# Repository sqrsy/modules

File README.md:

# What is it?

This folder contains Eurorack modules (PCBs and panels) that I designed. They are all open to use, but you must make any derivatives open too. If you use them commercially, please donate 10% of profits to a charity nearby you.

I will add detailed part lists and assembly instructions if and when I make them.

# Modules

* cv-mixer (6hp): uses an op-amp to perform attenuversion and addition on 3 inputs.
	* Parts: thonk jacks, thonk 50k pots, {560, 100k, 1M} resistors, 0.1 uF capacitors, tl074 op-amps, 10-pin power.

* logic (8hp): two sets of 2-input, 3-output logic gates: or, and, xor.
	* Parts: thonk jacks, {5k, 150k} resistors, 3mm LEDs, 4030 IC, 4071 IC, 4081 IC, 16-pin power.
	* Note: this is an imperfect module. It is missing an input comparator and an output buffer, and has untied pins on the unused logic gates.

* hocketman (8hp): an Arduino Nano Every hocket device that routes input depending on the note played.
	* Parts: thonk jacks, thonk 50k pots, thonk switches, {150k, 220k} resistors, mcp4822, 10-pin power.

* quantiser (8hp): an Arduino Nano Every dual quantiser with scale controlled by switches.
	* Parts: thonk jacks, thonk 50k pots, thonk switches, {150k, 220k} resistors, mcp4822, 10-pin power.

* rasa3x2 (10hp): a generic 2-input, 6-parameter, 4-switch, 2-output Arduino Nano Every Eurorack module shield with DAC and optional thru-zero voltage output.
	* Parts: thonk jacks, thonk 50k pots, thonk switches (optional), {330, 500, 1k, 10k, 20k, 100k} resistors, 3mm LEDs, mcp4822, 16-pin power.

* rasa6 (6hp): a generic 1-input, 2-parameter, 2-output Arduino Beetle Eurorack module shield with optional DAC.
	* Parts: thonk jacks, thonk 50k pots, {150k, 220k} resistors, mcp4822 (optional), 16-pin power.

* sn76489 (8hp): exposes the sn76489 chip as a Eurorack module.
	* Parts: thonk jacks, thonk 50k pots, thonk sub-mini switch, {150k, 220k} resistors, sn76489, 16-pin power.

* switch (3hp): a 6-jack mult that can route a 2-jack mult to one of two different sets of 2-jack mults.
	* Parts: thonk jacks, thonk sub-mini switch.

# Disclaimer

All files are provided without any guarantee. If you notice a mistake, please submit an Issue and I will fix it.

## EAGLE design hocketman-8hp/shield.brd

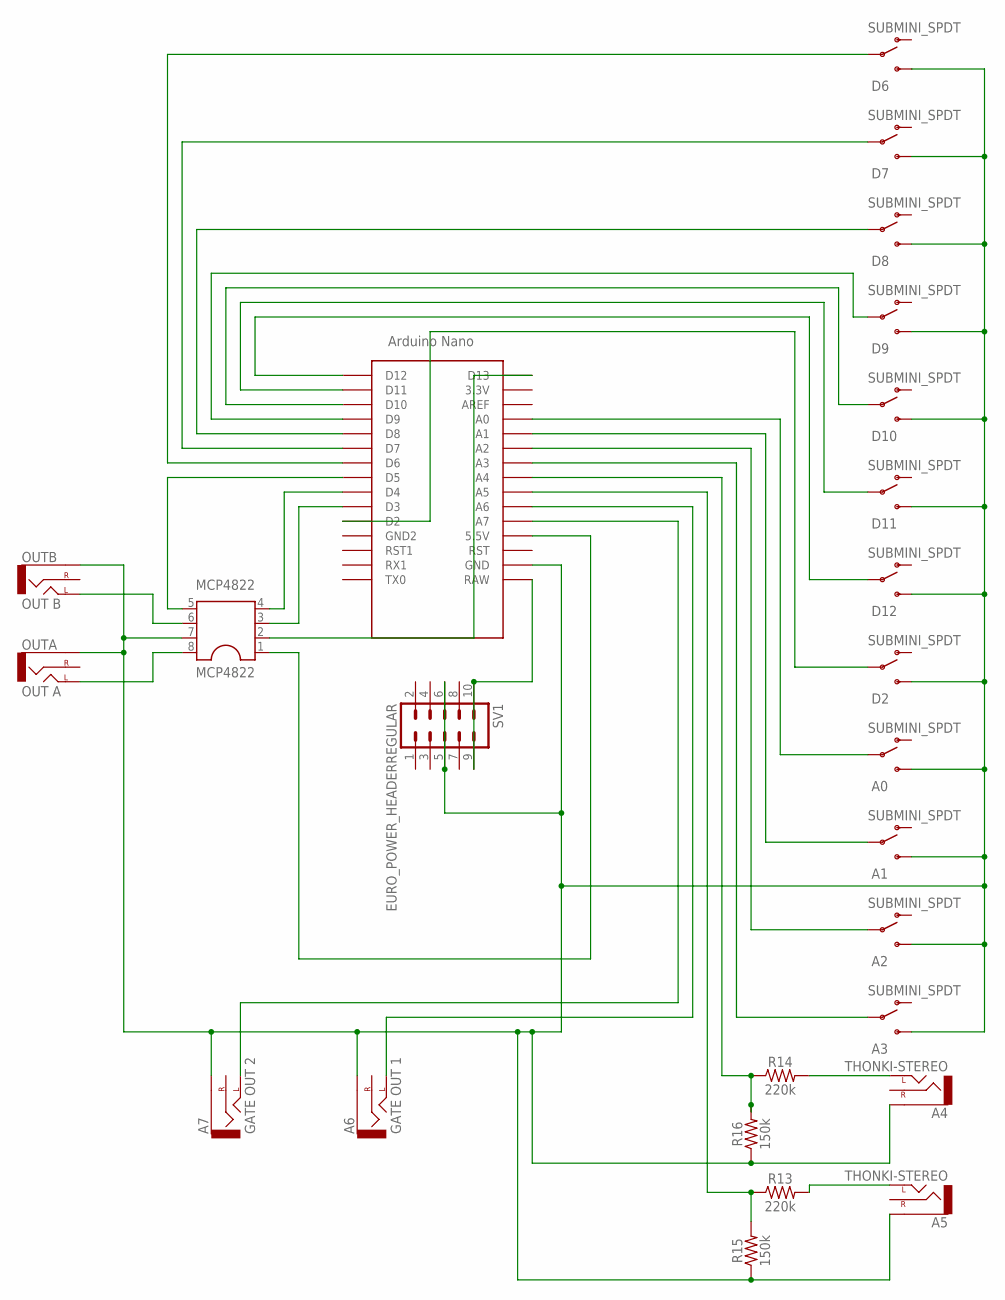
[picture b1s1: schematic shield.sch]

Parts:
A0, A1, A2, A3: SUBMINI_SPDT; SUBMINI_TOGGLE
A4, A5: THONKI-STEREO; WQP-PJ366ST_JACK
A6: GATE OUT 1; WQP-PJ366ST_JACK
A7: GATE OUT 2; WQP-PJ366ST_JACK
D2, D6, D7, D8, D9, D10, D11, D12: SUBMINI_SPDT; SUBMINI_TOGGLE
MCP4822: MCP4822; DIL08
OUTA: OUT A; WQP-PJ366ST_JACK
OUTB: OUT B; WQP-PJ366ST_JACK
R13, R14: 220k; AXIAL-0.3
R15, R16: 150k; AXIAL-0.3
SV1: EURO_POWER_HEADERREGULAR; EURO_POWER_HEADER
U$1: NANO

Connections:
unnamed: SV1.9, SV1.10, U$1.RAW
unnamed: A6.P$1_TIP (LEFT), U$1.A6
unnamed: MCP4822.1, U$1.5V (5.5V)
unnamed: D6.COM (COMMON), U$1.D6
unnamed: D7.COM (COMMON), U$1.D7
unnamed: A7.P$1_TIP (LEFT), U$1.A7
unnamed: D9.COM (COMMON), U$1.D9
unnamed: D10.COM (COMMON), U$1.D10
unnamed: D11.COM (COMMON), U$1.D11
unnamed: D12.COM (COMMON), U$1.D12
unnamed: D2.COM (COMMON), U$1.D2
unnamed: A0.COM (COMMON), U$1.A0
unnamed: A1.COM (COMMON), U$1.A1
unnamed: A2.COM (COMMON), U$1.A2
unnamed: A3.COM (COMMON), U$1.A3
unnamed: MCP4822.8, OUTA.P$1_TIP (LEFT)
unnamed: MCP4822.6, OUTB.P$1_TIP (LEFT)
unnamed: MCP4822.2, U$1.D13
unnamed: MCP4822.3, U$1.D3
unnamed: MCP4822.4, U$1.D4
unnamed: MCP4822.5, U$1.D5
unnamed: A0.3 (S), A1.3 (S), A2.3 (S), A3.3 (S), A4.P$3_SLEEVE (SLEEVE), A5.P$3_SLEEVE (SLEEVE), A6.P$3_SLEEVE (SLEEVE), A7.P$3_SLEEVE (SLEEVE), D2.3 (S), D6.3 (S), D7.3 (S), D8.3 (S), D9.3 (S), D10.3 (S), D11.3 (S), D12.3 (S), MCP4822.7, OUTA.P$3_SLEEVE (SLEEVE), OUTB.P$3_SLEEVE (SLEEVE), R15.P$1 (1), R16.P$1 (1), SV1.5, SV1.6, U$1.GND
unnamed: D8.COM (COMMON), U$1.D8
unnamed: A5.P$1_TIP (LEFT), R13.P$2 (2)
unnamed: A4.P$1_TIP (LEFT), R14.P$2 (2)
unnamed: R14.P$1 (1), R16.P$2 (2), U$1.A4
unnamed: R13.P$1 (1), R15.P$2 (2), U$1.A5

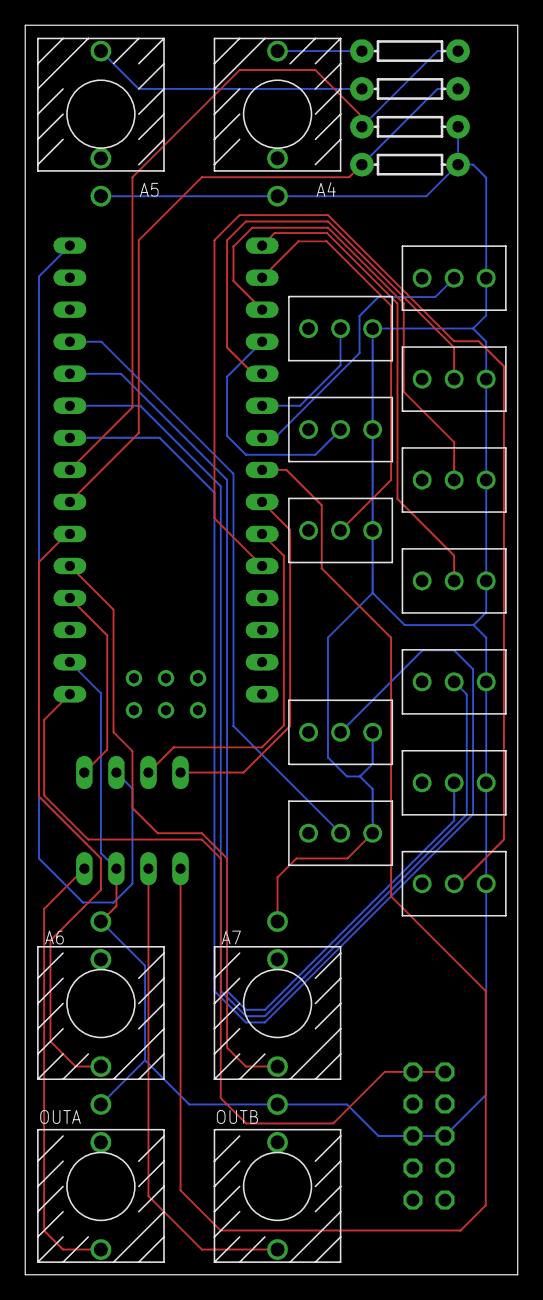
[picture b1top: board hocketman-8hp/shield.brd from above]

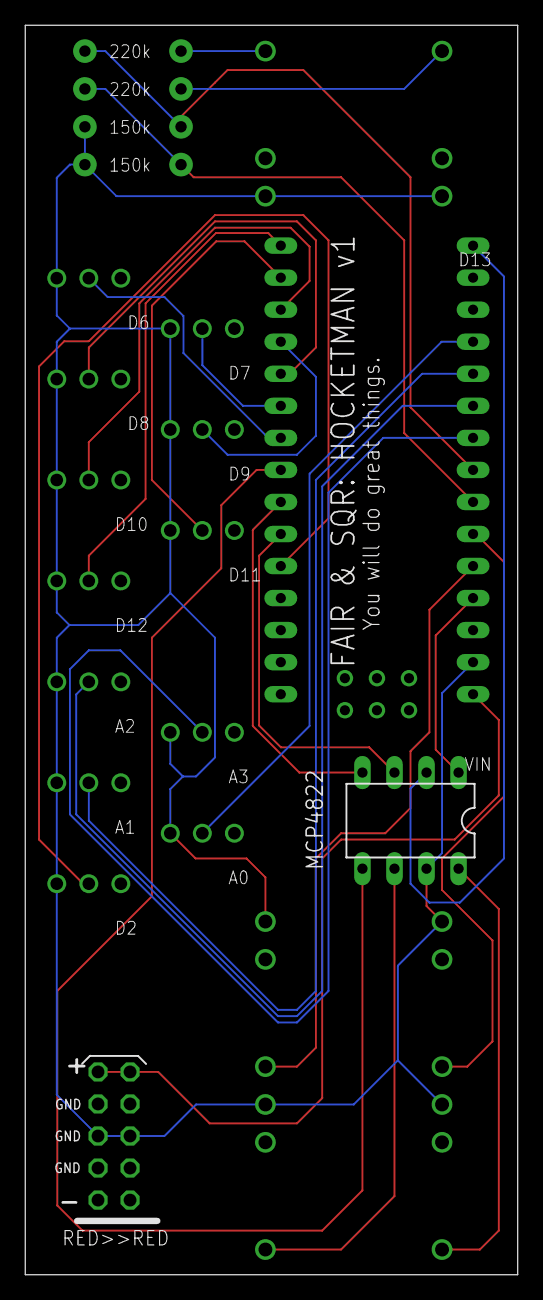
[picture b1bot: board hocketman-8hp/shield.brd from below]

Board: 2 copper layers, 39.0 x 99.0 mm, 25 parts (2 on the bottom side), 27 nets.

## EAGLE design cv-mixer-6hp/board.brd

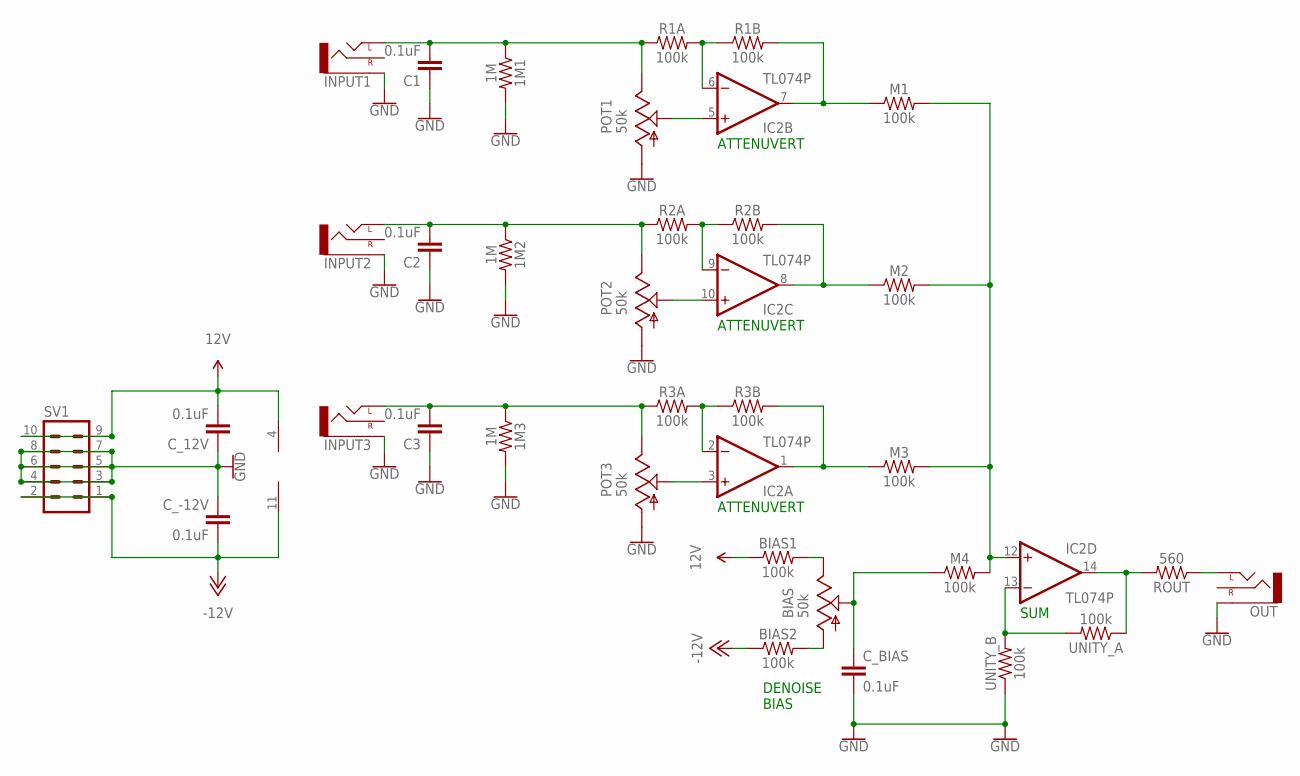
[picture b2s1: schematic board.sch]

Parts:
1M1, 1M2, 1M3: 1M; AXIAL-0.3
BIAS: 50k; 9MM_SNAP-IN_POT
BIAS1, BIAS2: 100k; AXIAL-0.3
C1, C2, C3: 0.1uF; CAP-PTH-SMALL-KIT
C_12V: 0.1uF; CAP-PTH-SMALL-KIT
C_-12V: 0.1uF; CAP-PTH-SMALL-KIT
C_BIAS: 0.1uF; CAP-PTH-SMALL-KIT
IC2: TL074P; DIL14
INPUT1, INPUT2, INPUT3: THONKI-STEREO; WQP-PJ366ST_JACK
M1, M2, M3, M4: 100k; AXIAL-0.3
OUT: THONKI-STEREO; WQP-PJ366ST_JACK
POT1, POT2, POT3: 50k; 9MM_SNAP-IN_POT
R1A, R1B, R2A, R2B, R3A, R3B: 100k; AXIAL-0.3
ROUT: 560; AXIAL-0.3
SV1: EURO_POWER_HEADERFAT_PADS; EURO_PWR_HEADER_FAT
UNITY_A: 100k; AXIAL-0.3
UNITY_B: 100k; AXIAL-0.3

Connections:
12V: BIAS1.P$1 (1), C_12V.2, IC2.4 (V+), SV1.9, SV1.10
-12V: BIAS2.P$1 (1), C_-12V.2, IC2.11 (V-), SV1.1, SV1.2
GND: 1M1.P$2 (2), 1M2.P$2 (2), 1M3.P$2 (2), C1.1, C2.1, C3.1, C_12V.1, C_-12V.1, C_BIAS.2, INPUT1.P$3_SLEEVE (SLEEVE), INPUT2.P$3_SLEEVE (SLEEVE), INPUT3.P$3_SLEEVE (SLEEVE), OUT.P$3_SLEEVE (SLEEVE), POT1.1 (A), POT2.1 (A), POT3.1 (A), SV1.3, SV1.4, SV1.5, SV1.6, SV1.7, SV1.8, UNITY_B.P$1 (1)
unnamed: OUT.P$1_TIP (LEFT), ROUT.P$1 (1)
unnamed: IC2.14 (OUT), ROUT.P$2 (2), UNITY_A.P$1 (1)
unnamed: BIAS.3 (E), BIAS1.P$2 (2)
unnamed: BIAS.1 (A), BIAS2.P$2 (2)
unnamed: BIAS.2 (S), C_BIAS.1, M4.P$1 (1)
unnamed: IC2.12 (+IN), M1.P$2 (2), M2.P$2 (2), M3.P$2 (2), M4.P$2 (2)
unnamed: IC2.13 (-IN), UNITY_A.P$2 (2), UNITY_B.P$2 (2)
unnamed: IC2.7 (OUT), M1.P$1 (1), R1B.P$2 (2)
unnamed: IC2.6 (-IN), R1A.P$2 (2), R1B.P$1 (1)
unnamed: 1M1.P$1 (1), C1.2, INPUT1.P$1_TIP (LEFT), POT1.3 (E), R1A.P$1 (1)
unnamed: IC2.5 (+IN), POT1.2 (S)
unnamed: IC2.8 (OUT), M2.P$1 (1), R2B.P$2 (2)
unnamed: IC2.9 (-IN), R2A.P$2 (2), R2B.P$1 (1)
unnamed: 1M2.P$1 (1), C2.2, INPUT2.P$1_TIP (LEFT), POT2.3 (E), R2A.P$1 (1)
unnamed: IC2.10 (+IN), POT2.2 (S)
unnamed: IC2.1 (OUT), M3.P$1 (1), R3B.P$2 (2)
unnamed: IC2.2 (-IN), R3A.P$2 (2), R3B.P$1 (1)
unnamed: 1M3.P$1 (1), C3.2, INPUT3.P$1_TIP (LEFT), POT3.3 (E), R3A.P$1 (1)
unnamed: IC2.3 (+IN), POT3.2 (S)

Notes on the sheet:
SUM
DENOISE BIAS
ATTENUVERT

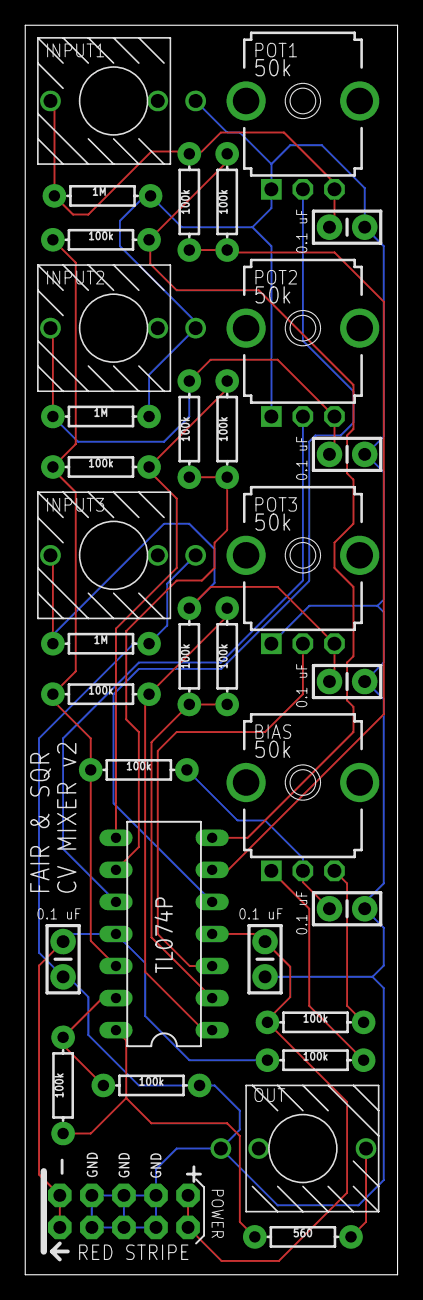
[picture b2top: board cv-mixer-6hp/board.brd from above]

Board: 2 copper layers, 29.5 x 99.0 mm, 34 parts (0 on the bottom side), 22 nets.

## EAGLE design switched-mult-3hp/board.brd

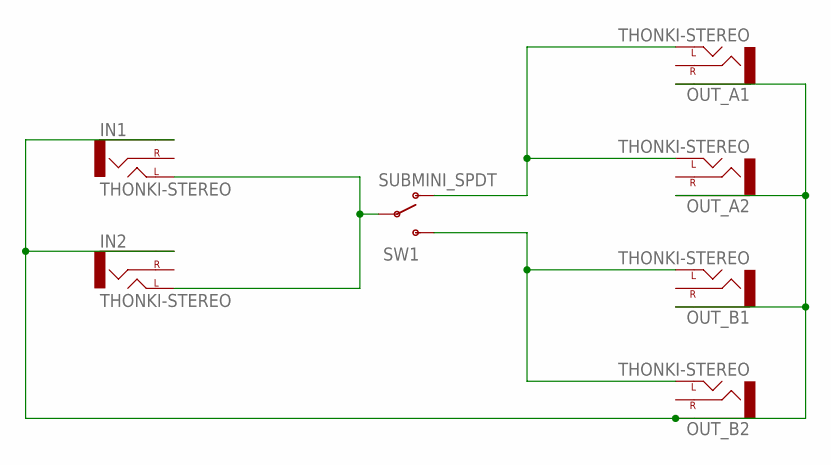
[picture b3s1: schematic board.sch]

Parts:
IN1, IN2: THONKI-STEREO; WQP-PJ366ST_JACK
OUT_A1, OUT_A2: THONKI-STEREO; WQP-PJ366ST_JACK
OUT_B1, OUT_B2: THONKI-STEREO; WQP-PJ366ST_JACK
SW1: SUBMINI_SPDT; SUBMINI_TOGGLE

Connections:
unnamed: IN1.P$1_TIP (LEFT), IN2.P$1_TIP (LEFT), SW1.COM (COMMON)
unnamed: OUT_A1.P$1_TIP (LEFT), OUT_A2.P$1_TIP (LEFT), SW1.1 (O)
unnamed: OUT_B1.P$1_TIP (LEFT), OUT_B2.P$1_TIP (LEFT), SW1.3 (S)
unnamed: IN1.P$3_SLEEVE (SLEEVE), IN2.P$3_SLEEVE (SLEEVE), OUT_A1.P$3_SLEEVE (SLEEVE), OUT_A2.P$3_SLEEVE (SLEEVE), OUT_B1.P$3_SLEEVE (SLEEVE), OUT_B2.P$3_SLEEVE (SLEEVE)

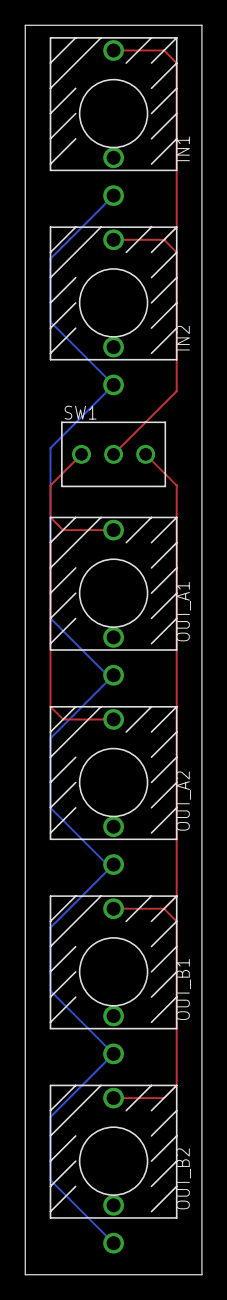
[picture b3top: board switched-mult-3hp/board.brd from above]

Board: 2 copper layers, 14.0 x 99.0 mm, 7 parts (0 on the bottom side), 4 nets.

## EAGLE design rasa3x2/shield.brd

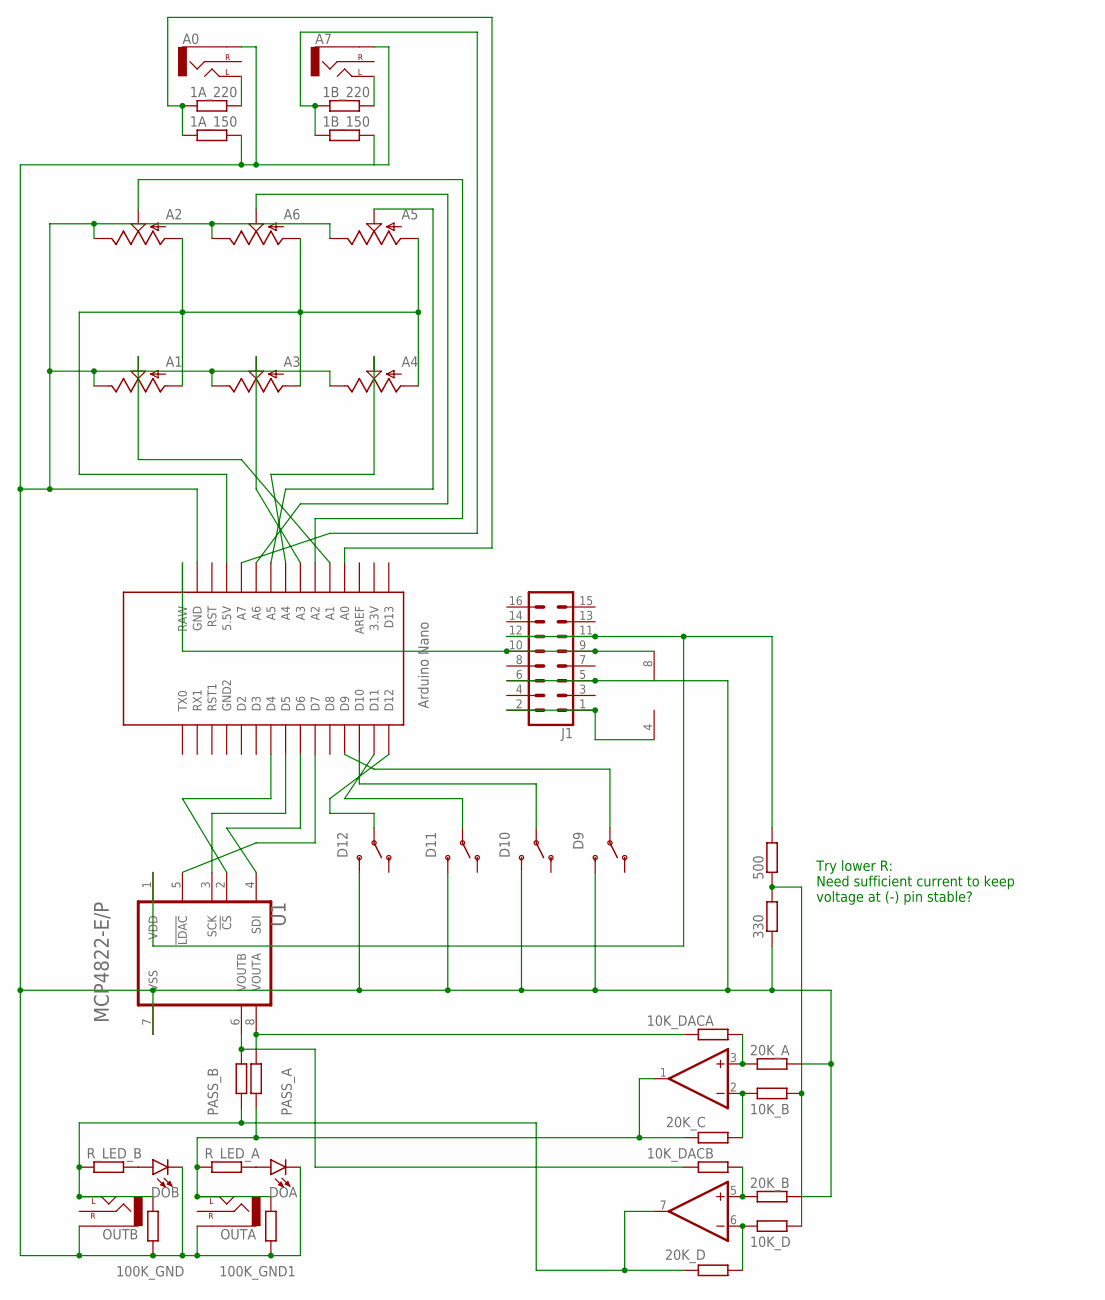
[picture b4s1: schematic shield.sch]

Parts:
1A_150, 1A_220, 1B_150, 1B_220, 10K_B, 10K_D, 10K_DACA, 10K_DACB, 20K_A, 20K_B, 20K_C, 20K_D, 100K_GND, 100K_GND1, 330, 500: RESISTOR7MM; 7MM_RESISTOR
A0, A7: THONKI-STEREO; WQP-PJ366ST_JACK
A1, A2, A3, A4, A5, A6: 9MM_SNAP-IN_POT_; 9MM_SNAP-IN_POT
D9, D10, D11, D12: SUBMINI_SPDT; SUBMINI_TOGGLE
DOA: LED3MM; LED_3MM
DOB: LED3MM; LED_3MM
IC1: TL072P; DIL08
J1: CONN_08X2; 2X8
OUTA: THONKI-STEREO; WQP-PJ366ST_JACK
OUTB: THONKI-STEREO; WQP-PJ366ST_JACK
PASS_A: RESISTOR7MM; 7MM_RESISTOR
PASS_B: RESISTOR7MM; 7MM_RESISTOR
R_LED_A: RESISTOR7MM; 7MM_RESISTOR
R_LED_B: RESISTOR7MM; 7MM_RESISTOR
U1: MICROCHIP_MCP4822-E-PMICROCHIP_MCP4822-E-P_0_0; MICROCHIP_MCP4822-E-P_0
U$1: NANO

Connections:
unnamed: D12.COM (COMMON), U$1.D12
unnamed: D11.COM (COMMON), U$1.D11
unnamed: A1.2 (S), U$1.A1
unnamed: 1A_150.2, 1B_150.2, 20K_A.2, 20K_B.2, 100K_GND.2, 100K_GND1.2, 330.1, A0.P$3_SLEEVE (SLEEVE), A1.3 (E), A2.3 (E), A3.3 (E), A4.3 (E), A5.3 (E), A6.3 (E), A7.P$3_SLEEVE (SLEEVE), D9.3 (S), D10.3 (S), D11.3 (S), D12.3 (S), DOA.K (C), DOB.K (C), J1.5, J1.6, OUTA.P$3_SLEEVE (SLEEVE), OUTB.P$3_SLEEVE (SLEEVE), U1.7 (VSS), U$1.GND
unnamed: D10.COM (COMMON), U$1.D10
unnamed: 1A_150.1, 1A_220.1, U$1.A0
unnamed: 1A_220.2, A0.P$1_TIP (LEFT)
unnamed: A1.1 (A), A2.1 (A), A3.1 (A), A4.1 (A), A5.1 (A), A6.1 (A), U$1.5V (5.5V)
unnamed: A2.2 (S), U$1.A2
unnamed: IC1.4 (V-), J1.1, J1.2
unnamed: A3.2 (S), U$1.A3
unnamed: A6.2 (S), U$1.A6
unnamed: 10K_DACA.1, PASS_A.2, U1.8 (VOUTA)
unnamed: 10K_DACB.1, PASS_B.2, U1.6 (VOUTB)
unnamed: A4.2 (S), U$1.A4
unnamed: 1B_150.1, 1B_220.1, U$1.A7
unnamed: A5.2 (S), U$1.A5
unnamed: 20K_C.2, 100K_GND1.1, IC1.1 (OUT), OUTA.P$1_TIP (LEFT), PASS_A.1, R_LED_A.1
unnamed: D9.COM (COMMON), U$1.D9
unnamed: 10K_D.1, 20K_D.1, IC1.6 (-IN)
unnamed: 10K_DACA.2, 20K_A.1, IC1.3 (+IN)
unnamed: 10K_B.1, 20K_C.1, IC1.2 (-IN)
unnamed: 10K_DACB.2, 20K_B.1, IC1.5 (+IN)
unnamed: 1B_220.2, A7.P$1_TIP (LEFT)
unnamed: 10K_B.2, 10K_D.2, 330.2, 500.1
unnamed: 20K_D.2, 100K_GND.1, IC1.7 (OUT), OUTB.P$1_TIP (LEFT), PASS_B.1, R_LED_B.1
unnamed: U1.2 (!CS!), U$1.D4
unnamed: U1.3 (SCK), U$1.D5
unnamed: U1.4 (SDI), U$1.D6
unnamed: U1.5 (!LDAC!), U$1.D7
unnamed: DOB.A, R_LED_B.2
unnamed: DOA.A, R_LED_A.2
unnamed: 500.2, J1.11, J1.12, U1.1 (VDD)
unnamed: IC1.8 (V+), J1.9, J1.10, U$1.RAW

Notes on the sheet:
Try lower R: Need sufficient current to keep voltage at (-) pin stable?

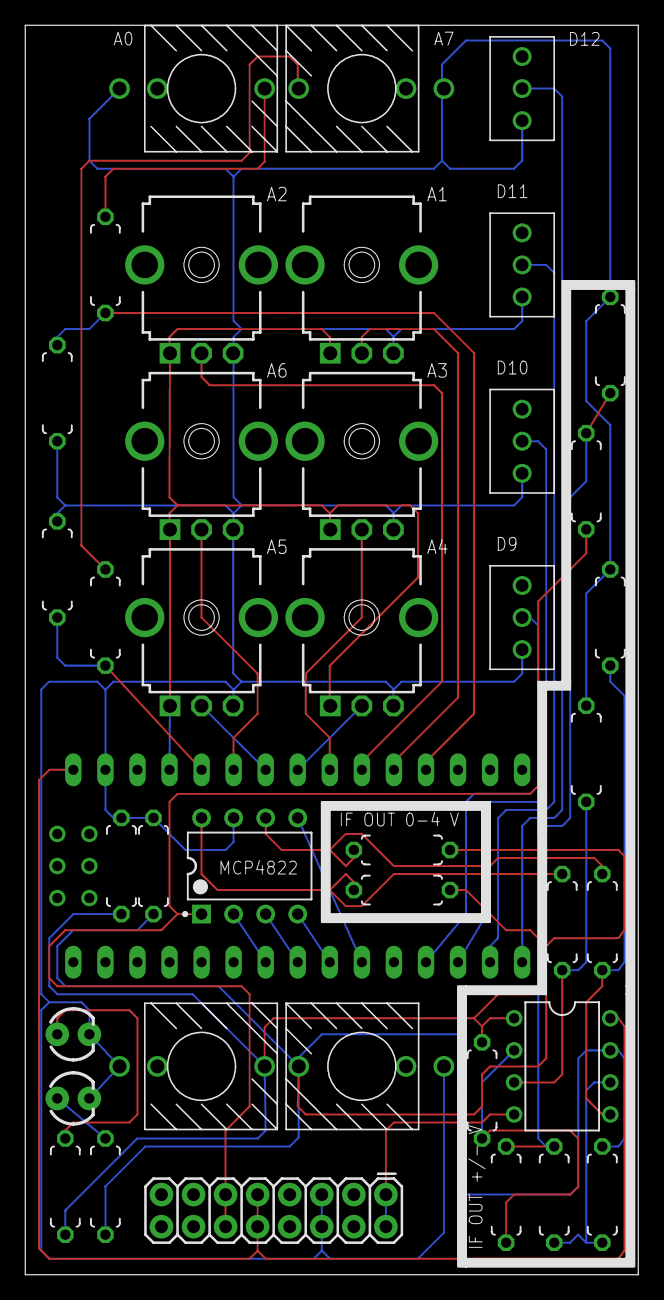
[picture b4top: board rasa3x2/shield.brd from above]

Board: 2 copper layers, 48.6 x 99.0 mm, 40 parts (0 on the bottom side), 34 nets.

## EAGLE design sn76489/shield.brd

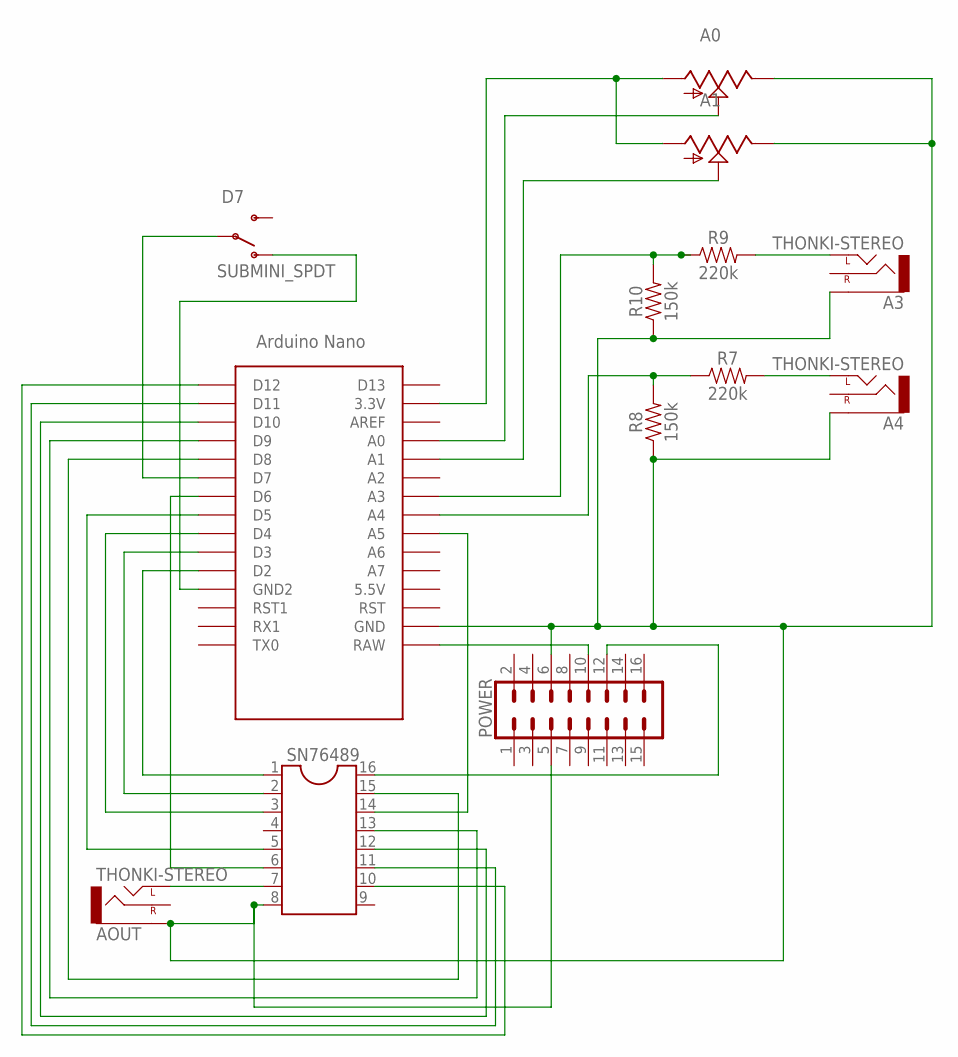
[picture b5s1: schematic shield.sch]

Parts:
A0, A1: 9MM_SNAP-IN_POT_; 9MM_SNAP-IN_POT
A3, A4: THONKI-STEREO; WQP-PJ366ST_JACK
AOUT: THONKI-STEREO; WQP-PJ366ST_JACK
D7: SUBMINI_SPDT; SUBMINI_TOGGLE
POWER: CONN_08X2; 2X8
R7, R9: 220k; AXIAL-0.3-KIT
R8, R10: 150k; AXIAL-0.3-KIT
SN76489: DIL16
U$1: NANO

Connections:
unnamed: SN76489.14, U$1.A5
unnamed: POWER.12, SN76489.16
unnamed: A0.1 (A), A1.1 (A), U$1.3.3V
unnamed: SN76489.5, U$1.D5
unnamed: SN76489.6, U$1.D6
unnamed: SN76489.3, U$1.D4
unnamed: SN76489.1, U$1.D2
unnamed: SN76489.2, U$1.D3
unnamed: POWER.10, U$1.RAW
unnamed: A3.P$1_TIP (LEFT), R9.P$2 (2)
unnamed: AOUT.P$1_TIP (LEFT), SN76489.7
unnamed: SN76489.10, U$1.D12
unnamed: D7.1 (O), U$1.GND1 (GND2)
unnamed: A0.2 (S), U$1.A0
unnamed: A1.2 (S), U$1.A1
unnamed: R9.P$1 (1), R10.P$2 (2), U$1.A3
unnamed: A4.P$1_TIP (LEFT), R7.P$2 (2)
unnamed: R7.P$1 (1), R8.P$2 (2), U$1.A4
unnamed: D7.COM (COMMON), U$1.D7
unnamed: A0.3 (E), A1.3 (E), A3.P$3_SLEEVE (SLEEVE), A4.P$3_SLEEVE (SLEEVE), AOUT.P$3_SLEEVE (SLEEVE), POWER.5, POWER.6, R8.P$1 (1), R10.P$1 (1), SN76489.8, U$1.GND
unnamed: SN76489.11, U$1.D11
unnamed: SN76489.13, U$1.D9
unnamed: SN76489.15, U$1.D8
unnamed: SN76489.12, U$1.D10

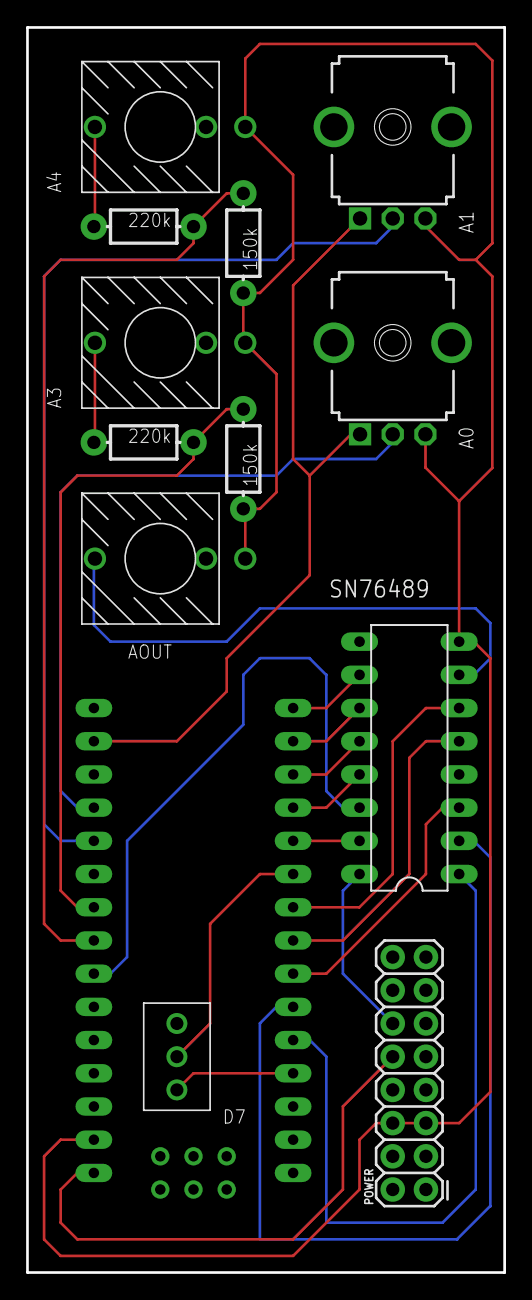
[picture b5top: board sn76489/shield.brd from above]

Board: 2 copper layers, 36.5 x 95.2 mm, 13 parts (0 on the bottom side), 24 nets.

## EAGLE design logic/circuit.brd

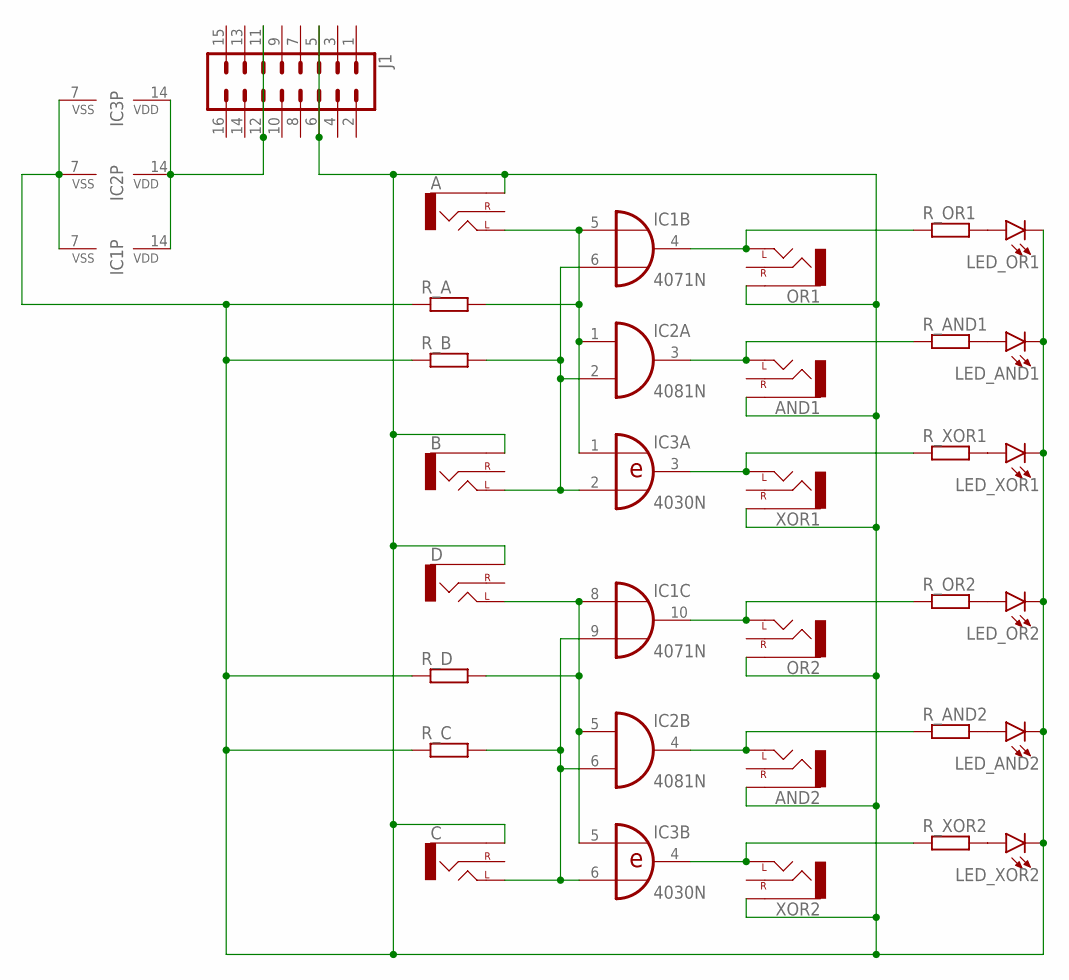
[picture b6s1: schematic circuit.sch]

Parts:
A: THONKI-STEREO; WQP-PJ366ST_JACK
AND1, AND2: THONKI-STEREO; WQP-PJ366ST_JACK
B: THONKI-STEREO; WQP-PJ366ST_JACK
C: THONKI-STEREO; WQP-PJ366ST_JACK
D: THONKI-STEREO; WQP-PJ366ST_JACK
IC1: 4071N; DIL14
IC2: 4081N; DIL14
IC3: 4030N; DIL14
J1: CONN_08X2; 2X8
LED_AND1, LED_AND2: LED3MM; LED_3MM
LED_OR1, LED_OR2: LED3MM; LED_3MM
LED_XOR1, LED_XOR2: LED3MM; LED_3MM
OR1, OR2: THONKI-STEREO; WQP-PJ366ST_JACK
R_A: RESISTOR7MM; 7MM_RESISTOR
R_AND1, R_AND2: RESISTOR7MM; 7MM_RESISTOR
R_B: RESISTOR7MM; 7MM_RESISTOR
R_C: RESISTOR7MM; 7MM_RESISTOR
R_D: RESISTOR7MM; 7MM_RESISTOR
R_OR1, R_OR2: RESISTOR7MM; 7MM_RESISTOR
R_XOR1, R_XOR2: RESISTOR7MM; 7MM_RESISTOR
XOR1, XOR2: THONKI-STEREO; WQP-PJ366ST_JACK

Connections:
LED_OR1: A.P$3_SLEEVE (SLEEVE), AND1.P$3_SLEEVE (SLEEVE), AND2.P$3_SLEEVE (SLEEVE), B.P$3_SLEEVE (SLEEVE), C.P$3_SLEEVE (SLEEVE), D.P$3_SLEEVE (SLEEVE), IC1.7 (VSS), IC2.7 (VSS), IC3.7 (VSS), J1.5, J1.6, LED_AND1.K (C), LED_AND2.K (C), LED_OR1.K (C), LED_OR2.K (C), LED_XOR1.K (C), LED_XOR2.K (C), OR1.P$3_SLEEVE (SLEEVE), OR2.P$3_SLEEVE (SLEEVE), R_A.1, R_B.1, R_C.1, R_D.1, XOR1.P$3_SLEEVE (SLEEVE), XOR2.P$3_SLEEVE (SLEEVE)
unnamed: LED_OR1.A, R_OR1.2
unnamed: LED_AND1.A, R_AND1.2
unnamed: IC1.14 (VDD), IC2.14 (VDD), IC3.14 (VDD), J1.11, J1.12
unnamed: LED_XOR1.A, R_XOR1.2
unnamed: LED_OR2.A, R_OR2.2
unnamed: LED_AND2.A, R_AND2.2
unnamed: LED_XOR2.A, R_XOR2.2
unnamed: IC3.4 (O), R_XOR2.1, XOR2.P$1_TIP (LEFT)
unnamed: AND2.P$1_TIP (LEFT), IC2.4 (O), R_AND2.1
unnamed: IC1.10 (O), OR2.P$1_TIP (LEFT), R_OR2.1
unnamed: IC3.3 (O), R_XOR1.1, XOR1.P$1_TIP (LEFT)
unnamed: AND1.P$1_TIP (LEFT), IC2.3 (O), R_AND1.1
unnamed: IC1.4 (O), OR1.P$1_TIP (LEFT), R_OR1.1
unnamed: A.P$1_TIP (LEFT), IC1.5 (I0), IC2.1 (I0), IC3.1 (I0), R_A.2
unnamed: B.P$1_TIP (LEFT), IC1.6 (I1), IC2.2 (I1), IC3.2 (I1), R_B.2
unnamed: D.P$1_TIP (LEFT), IC1.8 (I0), IC2.5 (I0), IC3.5 (I0), R_D.2
unnamed: C.P$1_TIP (LEFT), IC1.9 (I1), IC2.6 (I1), IC3.6 (I1), R_C.2

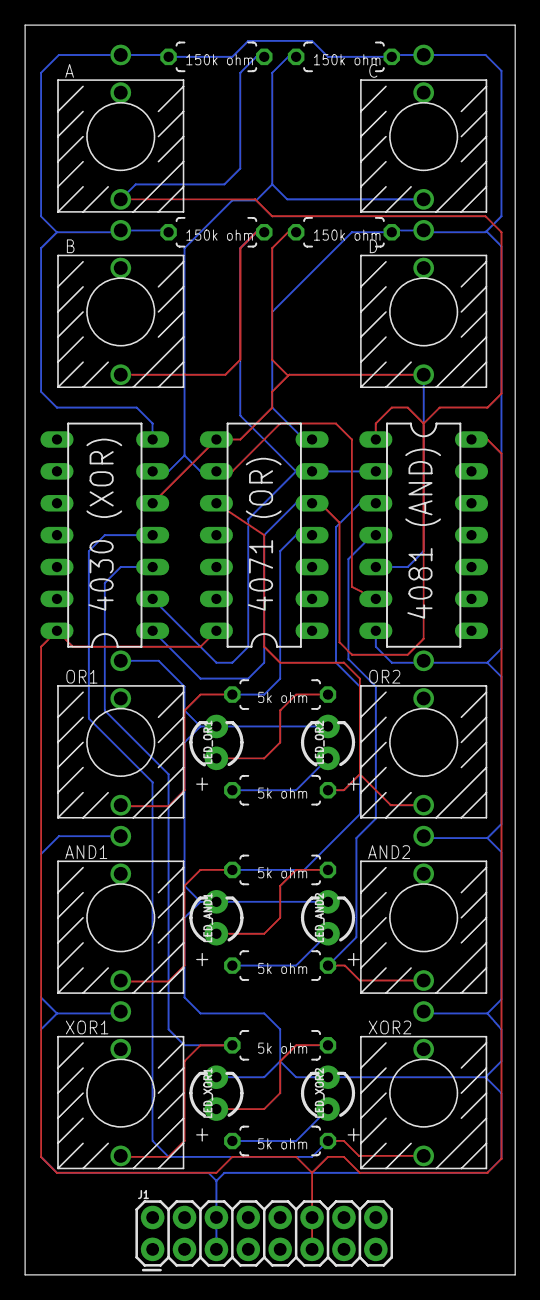
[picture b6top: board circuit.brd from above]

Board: 2 copper layers, 39.0 x 99.6 mm, 30 parts (0 on the bottom side), 18 nets.

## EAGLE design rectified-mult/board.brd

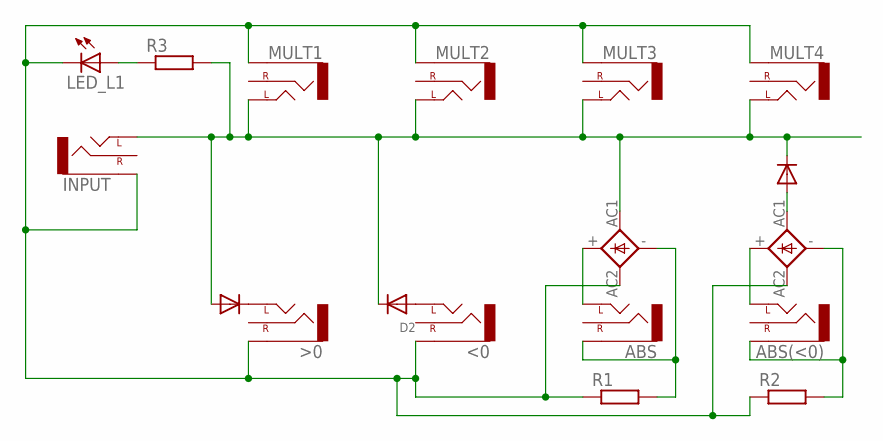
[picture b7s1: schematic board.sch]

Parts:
<0: THONKI-STEREO; WQP-PJ366ST_JACK
>0: THONKI-STEREO; WQP-PJ366ST_JACK
ABS: THONKI-STEREO; WQP-PJ366ST_JACK
ABS(<0): THONKI-STEREO; WQP-PJ366ST_JACK
B1, B2: 2KBB-R
D1, D2, D3: DIODEDO-1N4148; DO-1N4148
INPUT: THONKI-STEREO; WQP-PJ366ST_JACK
LED_L1: LED3MM
MULT1, MULT2, MULT3, MULT4: THONKI-STEREO; WQP-PJ366ST_JACK
R1, R2, R3: RESISTOR7MM; 7MM_RESISTOR

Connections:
unnamed: ABS(<0).P$1_TIP (LEFT), B2.+
unnamed: >0.P$1_TIP (LEFT), D1.C
unnamed: B2.AC1, D3.A
unnamed: LED_L1.A, R3.1
unnamed: <0.P$1_TIP (LEFT), D2.A
unnamed: B1.AC1, D1.A, D2.C, D3.C, INPUT.P$1_TIP (LEFT), MULT1.P$1_TIP (LEFT), MULT2.P$1_TIP (LEFT), MULT3.P$1_TIP (LEFT), MULT4.P$1_TIP (LEFT), R3.2
unnamed: <0.P$3_SLEEVE (SLEEVE), >0.P$3_SLEEVE (SLEEVE), B1.AC2, B2.AC2, INPUT.P$3_SLEEVE (SLEEVE), LED_L1.K (C), MULT1.P$3_SLEEVE (SLEEVE), MULT2.P$3_SLEEVE (SLEEVE), MULT3.P$3_SLEEVE (SLEEVE), MULT4.P$3_SLEEVE (SLEEVE), R1.1, R2.1
unnamed: ABS.P$3_SLEEVE (SLEEVE), B1.-, R1.2
unnamed: ABS.P$1_TIP (LEFT), B1.+
unnamed: ABS(<0).P$3_SLEEVE (SLEEVE), B2.-, R2.2

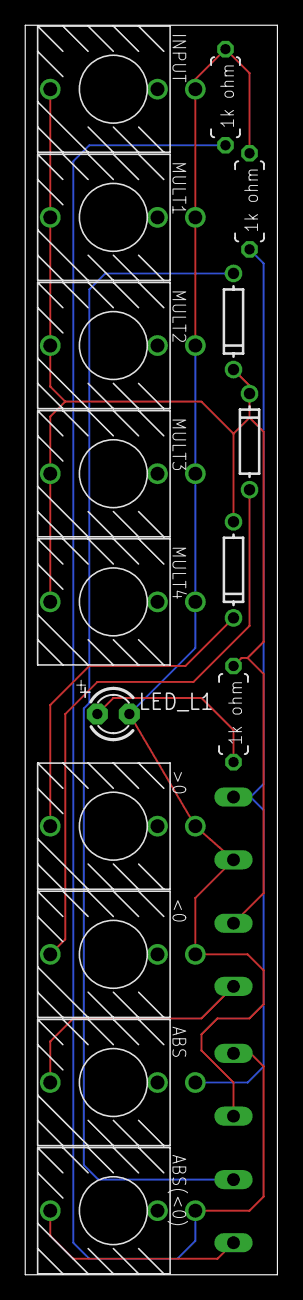
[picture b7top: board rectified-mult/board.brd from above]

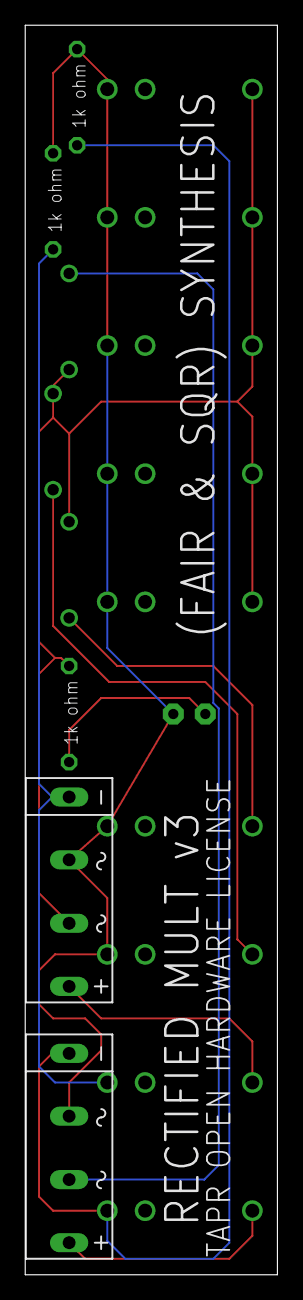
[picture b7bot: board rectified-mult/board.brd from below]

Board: 2 copper layers, 20.0 x 99.0 mm, 18 parts (2 on the bottom side), 10 nets.

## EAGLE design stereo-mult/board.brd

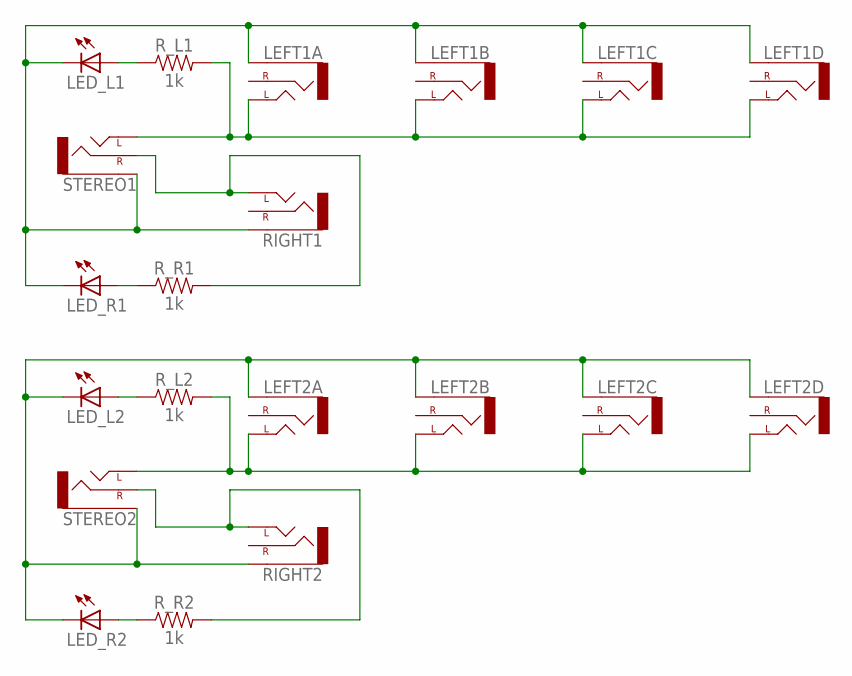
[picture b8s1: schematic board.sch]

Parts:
LED_L1, LED_L2: LED3MM
LED_R1, LED_R2: LED3MM
LEFT1A, LEFT1B, LEFT1C, LEFT1D, LEFT2A, LEFT2B, LEFT2C, LEFT2D: THONKI-STEREO; WQP-PJ366ST_JACK
RIGHT1, RIGHT2: THONKI-STEREO; WQP-PJ366ST_JACK
R_L1, R_L2: 1k; AXIAL-0.3
R_R1, R_R2: 1k; AXIAL-0.3
STEREO1, STEREO2: THONKI-STEREO; WQP-PJ366ST_JACK

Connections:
unnamed: LEFT1A.P$1_TIP (LEFT), LEFT1B.P$1_TIP (LEFT), LEFT1C.P$1_TIP (LEFT), LEFT1D.P$1_TIP (LEFT), R_L1.P$2 (2), STEREO1.P$1_TIP (LEFT)
unnamed: RIGHT1.P$1_TIP (LEFT), R_R1.P$2 (2), STEREO1.P$2_SWITCH (RIGHT)
unnamed: LED_L1.K (C), LED_R1.K (C), LEFT1A.P$3_SLEEVE (SLEEVE), LEFT1B.P$3_SLEEVE (SLEEVE), LEFT1C.P$3_SLEEVE (SLEEVE), LEFT1D.P$3_SLEEVE (SLEEVE), RIGHT1.P$3_SLEEVE (SLEEVE), STEREO1.P$3_SLEEVE (SLEEVE)
unnamed: LED_L1.A, R_L1.P$1 (1)
unnamed: LED_R1.A, R_R1.P$1 (1)
unnamed: LEFT2A.P$1_TIP (LEFT), LEFT2B.P$1_TIP (LEFT), LEFT2C.P$1_TIP (LEFT), LEFT2D.P$1_TIP (LEFT), R_L2.P$2 (2), STEREO2.P$1_TIP (LEFT)
unnamed: LED_L2.K (C), LED_R2.K (C), LEFT2A.P$3_SLEEVE (SLEEVE), LEFT2B.P$3_SLEEVE (SLEEVE), LEFT2C.P$3_SLEEVE (SLEEVE), LEFT2D.P$3_SLEEVE (SLEEVE), RIGHT2.P$3_SLEEVE (SLEEVE), STEREO2.P$3_SLEEVE (SLEEVE)
unnamed: RIGHT2.P$1_TIP (LEFT), R_R2.P$2 (2), STEREO2.P$2_SWITCH (RIGHT)
unnamed: LED_L2.A, R_L2.P$1 (1)
unnamed: LED_R2.A, R_R2.P$1 (1)

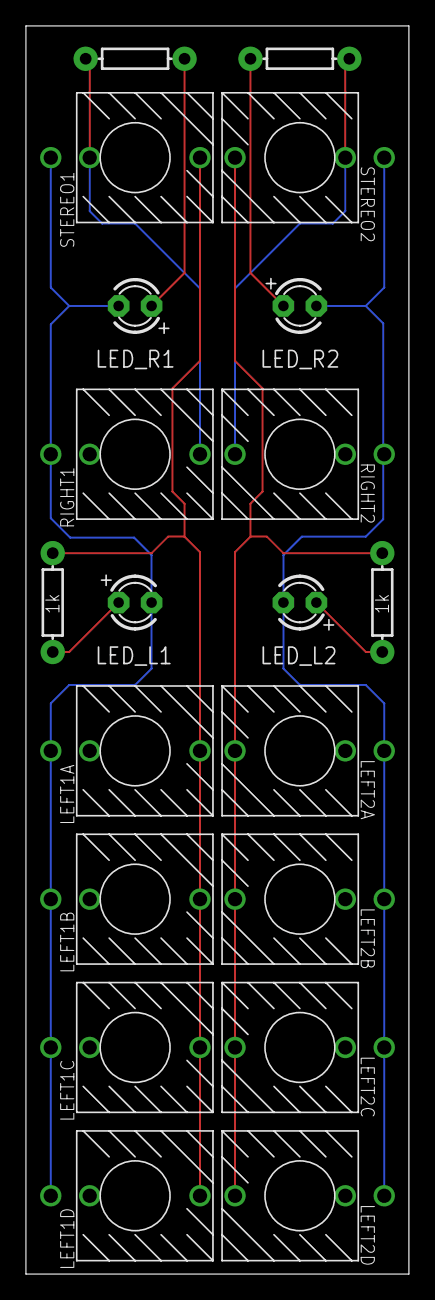
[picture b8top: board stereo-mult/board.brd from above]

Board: 2 copper layers, 29.5 x 96.2 mm, 20 parts (0 on the bottom side), 10 nets.

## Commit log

2023-07-26 Publish first two circuits
2023-07-26 Quick fix to readme
2023-07-28 Add Rasa6 modules and panels
2023-07-28 Fix Rasa 6 description
2023-08-14 Add files for two more mults
2023-08-14 Fix readme
2023-09-22 Add logic module
2023-10-08 Add a note to 2 modules
2023-10-08 Finalise name change
2023-10-08 Note addendum
2023-10-08 Fix mix up
2024-05-21 Get rid of calculate module
2024-05-21 Get rid of stereo-mult module
2024-05-21 Add stencil for switch-mult panel
2024-05-21 Add cv-mixer module
2024-05-21 Add sn76489 module
2024-06-02 Add rasa3x2 module
2024-11-05 Fix typo
2024-11-05 Add recent 3hp switched mult
2024-11-09 Add module hp to folder names
2024-11-10 Add quantiser module
2024-11-10 Add quantiser to README
2024-11-10 Add missing full stop
2025-02-02 Replace 7hp mixer with 6hp version
2025-02-02 Replace 12hp quantiser with 8hp version
2025-02-02 Add some rasa3x2 covers
2025-02-02 Add some rasa6 covers
2025-02-02 Refresh docs with new hp sizes
2025-04-19 Add new panel for logic module
2025-04-19 Add new panel for quantiser module
2025-04-19 Add hocketman module
2025-04-20 Add more panel options for Rasa6 module

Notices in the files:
rectified-mult/board.brd:
TAPR OPEN HARDWARE LICENSE
parts and their libraries:
SparkFun-LED: Licensing: Creative Commons ShareAlike 4.0 International - https://creativecommons.org/licenses/by-sa/4.0
